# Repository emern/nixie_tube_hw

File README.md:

# nixie_tube_hw
Hardware designed in KiCAD for IN-16 nixie tubes

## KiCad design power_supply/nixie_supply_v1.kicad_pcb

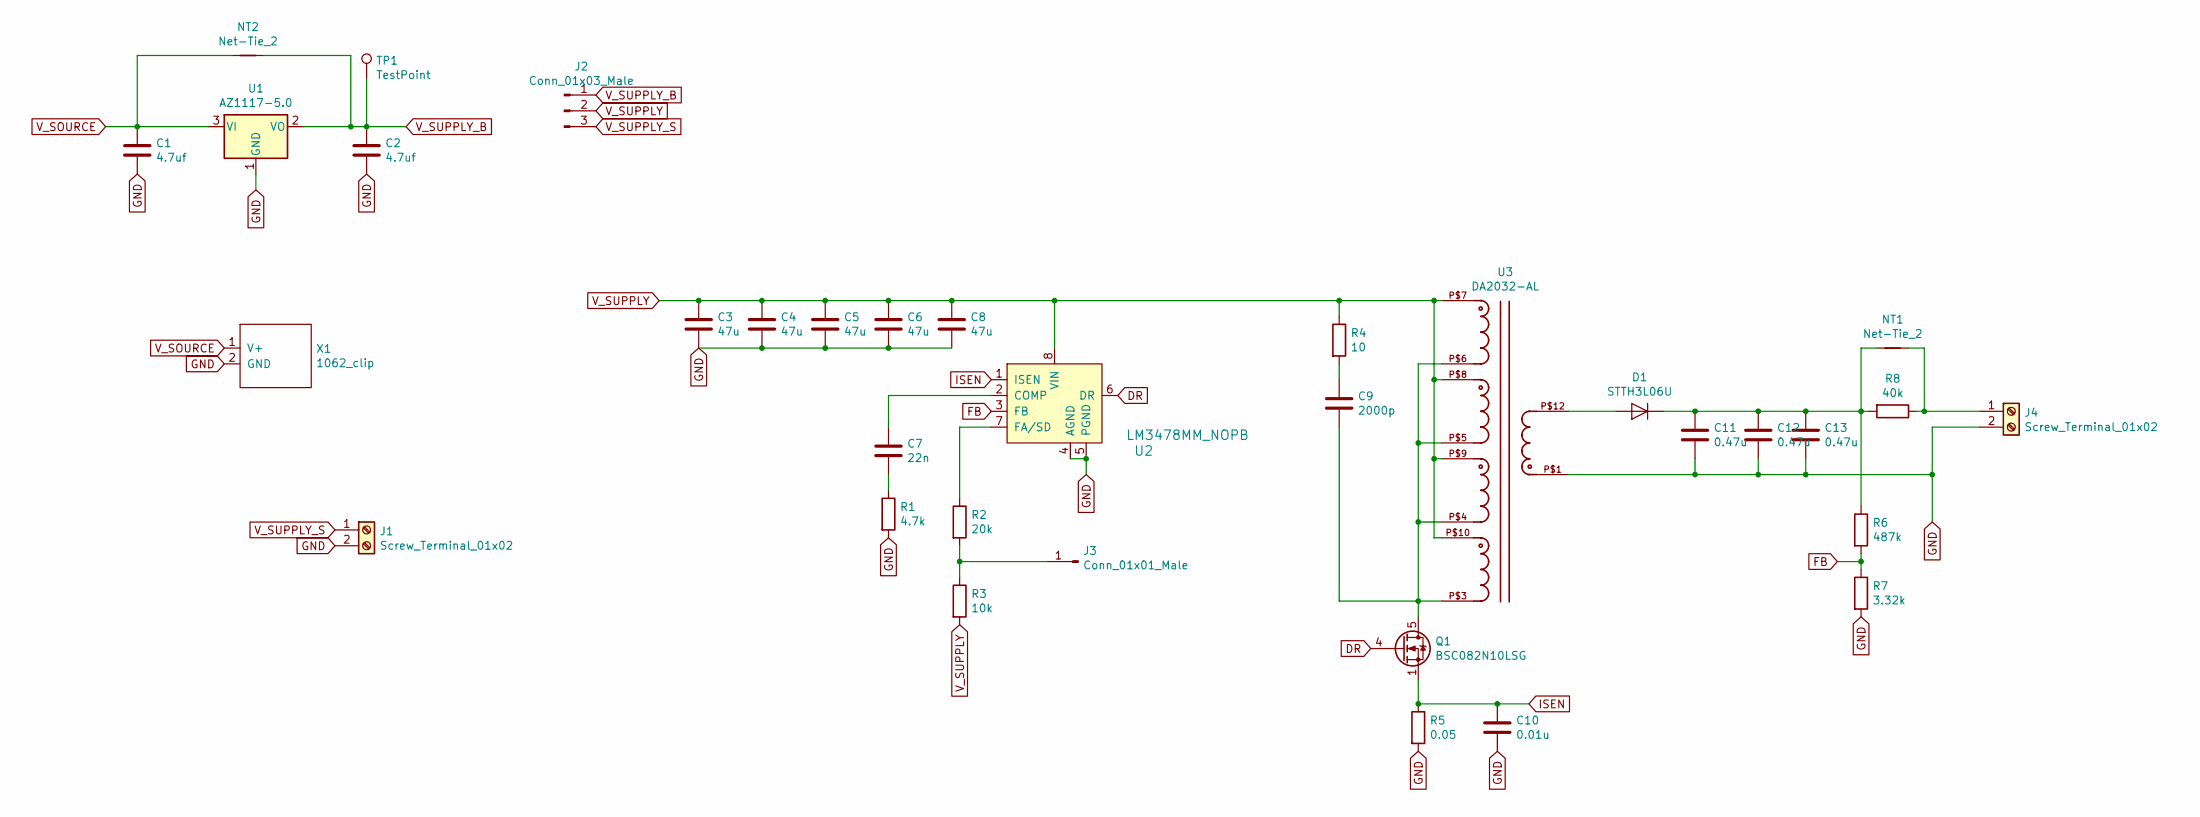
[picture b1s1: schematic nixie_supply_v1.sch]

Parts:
C1, C2: 4.7uf; C_0402_1005Metric
C3, C4, C5, C6, C8: 47u; C_0805_2012Metric
C7: 22n; C_0402_1005Metric
C9: 2000p; C_0603_1608Metric
C10: 0.01u; C_0603_1608Metric
C11, C12, C13: 0.47u; C_1210_3225Metric
D1: STTH3L06U; D_SMB
J1, J4: Screw_Terminal_01x02; 691214110002
J2: Conn_01x03_Male; PinHeader_1x03_P2.54mm_Vertical
J3: Conn_01x01_Male; PinHeader_1x01_P2.54mm_Vertical
NT1: Net-Tie_2; D_0805_2012Metric
NT2: Net-Tie_2; PinHeader_1x02_P2.54mm_Vertical
Q1: BSC082N10LSG; TDSON-8-1
R1: 4.7k; R_0805_2012Metric
R2: 20k; R_0603_1608Metric
R3: 10k; R_0603_1608Metric
R4: 10; R_0805_2012Metric
R5: 0.05; R_0402_1005Metric
R6: 487k; R_0805_2012Metric
R7: 3.32k; R_0603_1608Metric
R8: 40k; R_1206_3216Metric
TP1: TestPoint; TestPoint_Pad_D3.0mm
U1: AZ1117-5.0; SOT-223
U2: LM3478MM_NOPB; SOIC-8_W3.9mm; MPN LM3478MM/NOPB; Digi-Key_PN LM3478MM/NOPBCT-ND
U3: DA2032-AL
X1: 1062_clip

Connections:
DR: Q1.4 (G), U2.6 (DR)
FB: R6.2, R7.1, U2.3 (FB)
GND: C1.2, C2.2, C3.2, C4.2, C5.2, C6.2, C8.2, C10.2, C11.2, C12.2, C13.2, J1.2, J4.2, R1.2, R5.2, R7.2, U1.1 (GND), U2.4 (AGND), U2.5 (PGND), U3.P$1, X1.2 (GND)
ISEN: C10.1, Q1.1 (S), Q1.2 (S), Q1.3 (S), R5.1, U2.1 (ISEN)
unnamed: C7.1, U2.2 (COMP)
unnamed: C7.2, R1.1
unnamed: C9.1, R4.2
unnamed: C9.2, Q1.5 (D), U3.P$3, U3.P$4, U3.P$5, U3.P$6
unnamed: C11.1, C12.1, C13.1, D1.1 (K), NT1.1, R6.1, R8.2
unnamed: D1.2 (A), U3.P$12
unnamed: J3.1, R2.2, R3.1
unnamed: J4.1, NT1.2, R8.1
unnamed: R2.1, U2.7 (FA/SD)
V_SOURCE: C1.1, NT2.1, U1.3 (VI), X1.1 (V+)
V_SUPPLY: C3.1, C4.1, C5.1, C6.1, C8.1, J2.2, R3.2, R4.1, U2.8 (VIN), U3.P$7, U3.P$8, U3.P$9, U3.P$10
V_SUPPLY_B: C2.1, J2.1, NT2.2, TP1.1, U1.2 (VO)
V_SUPPLY_S: J1.1, J2.3

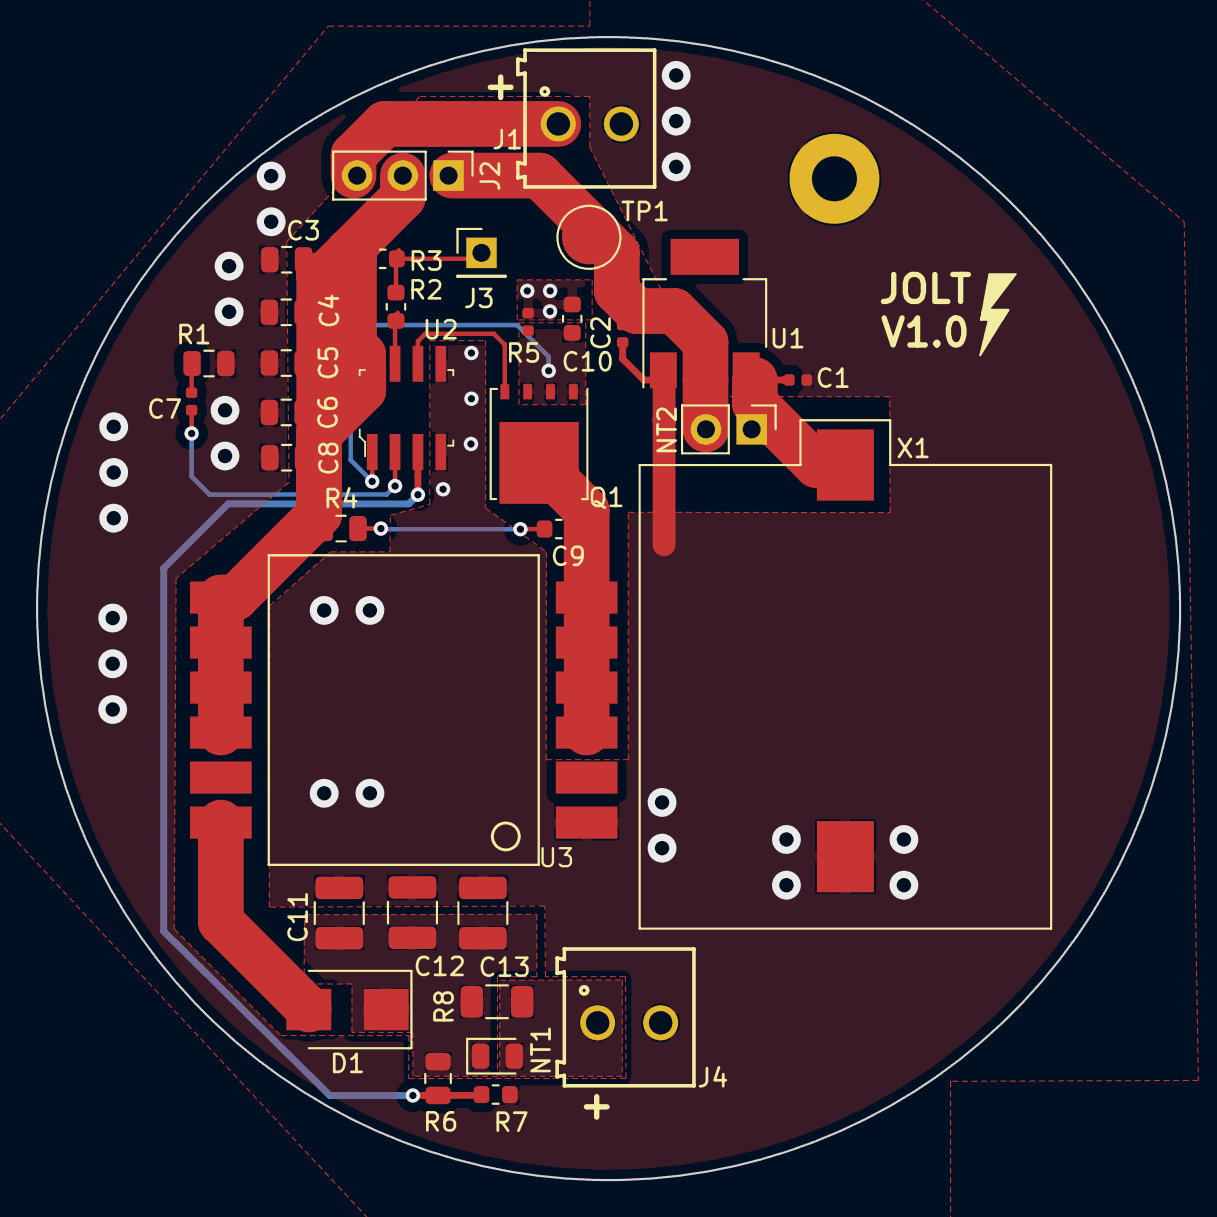
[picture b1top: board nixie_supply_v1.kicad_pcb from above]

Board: 4 copper layers, 63.5 x 63.5 mm, 34 parts (0 on the bottom side), 17 nets.

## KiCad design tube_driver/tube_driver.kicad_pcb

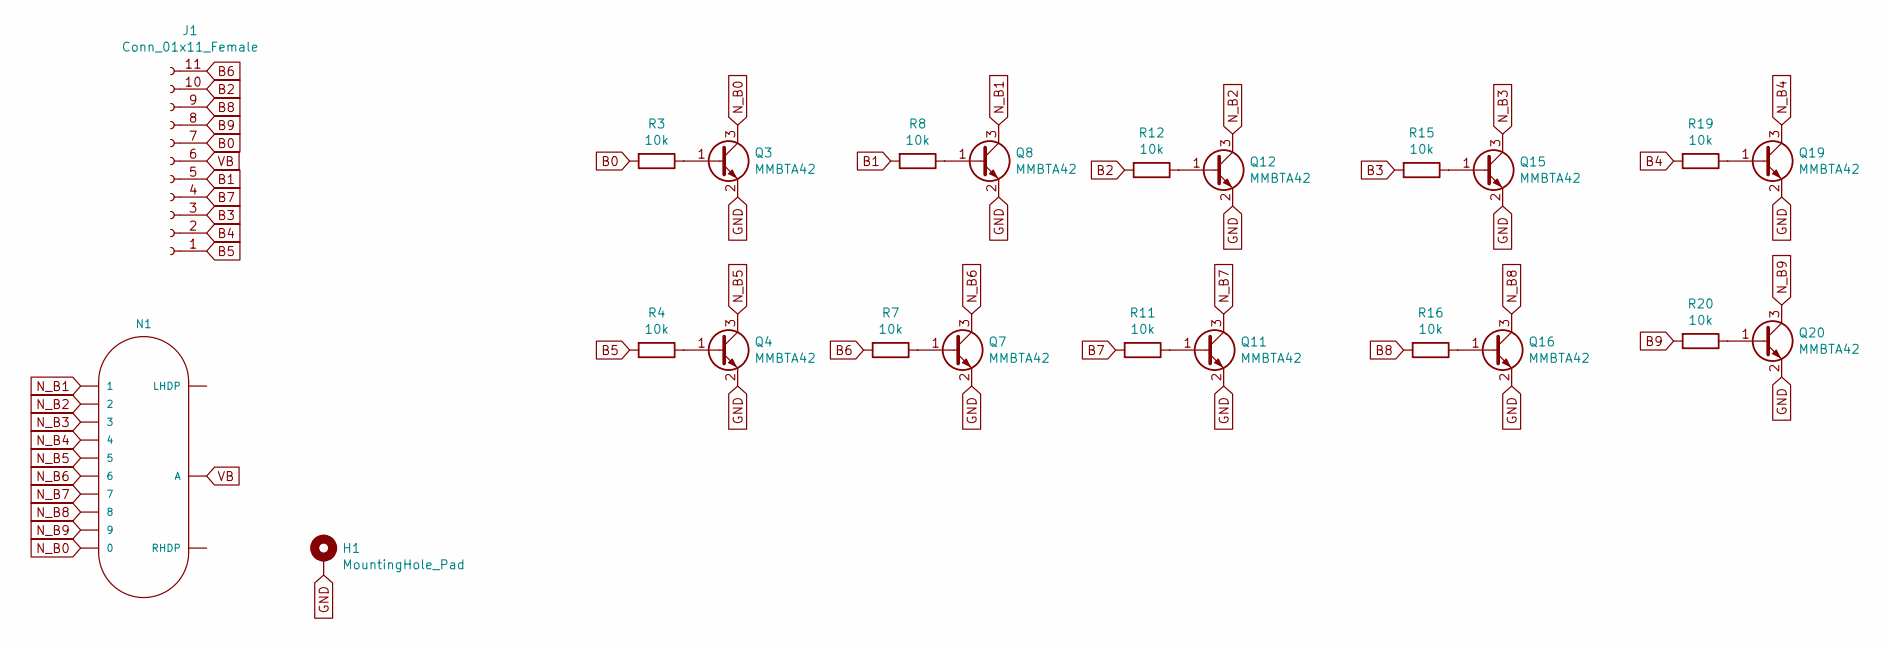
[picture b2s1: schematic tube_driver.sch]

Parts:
H1: MountingHole_Pad; MountingHole_2.7mm_M2.5_Pad
J1: Conn_01x11_Female; PinSocket_1x11_P2.54mm_Vertical
N1: IN-16; nixies-us-IN-16
Q3, Q4, Q7, Q8, Q11, Q12, Q15, Q16, Q19, Q20: MMBTA42; SOT-23
R3, R4, R7, R8, R11, R12, R15, R16, R19, R20: 10k; R_0402_1005Metric

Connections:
B0: J1.7, R3.2
B1: J1.5, R8.2
B2: J1.10, R12.2
B3: J1.3, R15.2
B4: J1.2, R19.2
B5: J1.1, R4.2
B6: J1.11, R7.2
B7: J1.4, R11.2
B8: J1.9, R16.2
B9: J1.8, R20.2
GND: H1.1, Q3.2 (E), Q4.2 (E), Q7.2 (E), Q8.2 (E), Q11.2 (E), Q12.2 (E), Q15.2 (E), Q16.2 (E), Q19.2 (E), Q20.2 (E)
N_B0: N1.0, Q3.3 (C)
N_B1: N1.1, Q8.3 (C)
N_B2: N1.2, Q12.3 (C)
N_B3: N1.3, Q15.3 (C)
N_B4: N1.4, Q19.3 (C)
N_B5: N1.5, Q4.3 (C)
N_B6: N1.6, Q7.3 (C)
N_B7: N1.7, Q11.3 (C)
N_B8: N1.8, Q16.3 (C)
N_B9: N1.9, Q20.3 (C)
unnamed: Q3.1 (B), R3.1
unnamed: Q4.1 (B), R4.1
unnamed: Q7.1 (B), R7.1
unnamed: Q8.1 (B), R8.1
unnamed: Q11.1 (B), R11.1
unnamed: Q12.1 (B), R12.1
unnamed: Q15.1 (B), R15.1
unnamed: Q16.1 (B), R16.1
unnamed: Q19.1 (B), R19.1
unnamed: Q20.1 (B), R20.1
VB: J1.6, N1.A

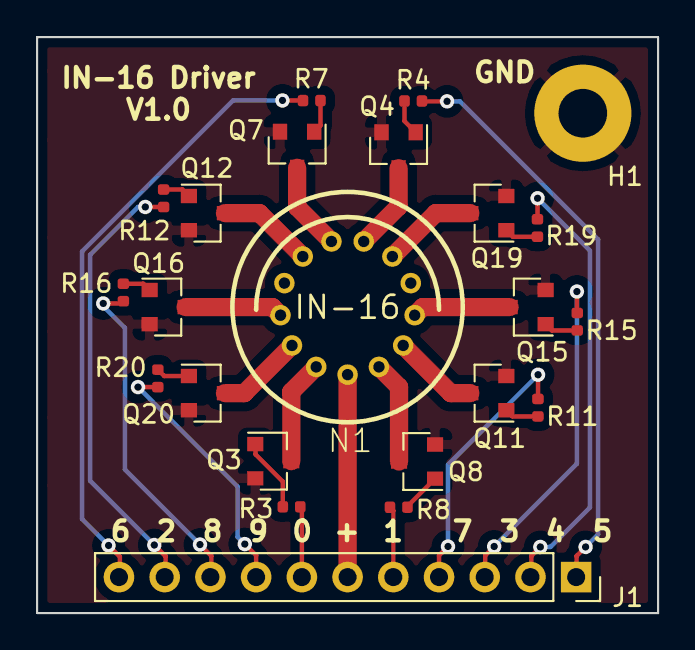
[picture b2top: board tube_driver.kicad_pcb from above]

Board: 6 copper layers, 34.5 x 32.0 mm, 23 parts (0 on the bottom side), 32 nets.

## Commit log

2021-12-28 add gitignore
2021-12-28 add tube driver and power supply
